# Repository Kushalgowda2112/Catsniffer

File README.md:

# **CatSniffer**

## Overview

CatSniffer 😼 is a multiprotocol, multiband device designed for sniffing, communicating, and attacking IoT (Internet of Things) devices. Shaped as a highly portable USB stick, it integrates powerful chips like **TI CC1352**, **Semtech SX1262**, and either the **RP2040** (for V3 and newer) or **Microchip SAMD21E17** (for V2 and earlier).

This device serves as a comprehensive tool for IoT security researchers, developers, and enthusiasts. CatSniffer is compatible with a wide range of software, including:

- SmartRF Packet Sniffer
- Sniffle
- zigbee2mqtt
- Z-Stack-firmware
- Ubiqua Protocol Analyzer
- Custom applications tailored to your specific needs

---

## Supported Technologies

CatSniffer can operate across multiple protocols:
- **LoRa**
- **Sub-1 GHz**
- **2.4 GHz**

Inspired by the work of Michael Ossmann and tools like the YardStick, GreatFET, HackRF, and Ubertooth, CatSniffer pays homage to the open-source hardware community.

---

## Versions

CatSniffer has evolved through several iterations, each improving on the previous:
- **CatSniffer v1.2**
- **CatSniffer v1.3**
- **CatSniffer v2.0**
- **CatSniffer v2.1**
- **CatSniffer v3.1**

All versions are supported, but newer versions include additional features and enhancements. Firmware for each version is tracked separately within the repository for clarity and ease of access.

---

## Protocols Supported

CatSniffer is compatible with the following protocols:
- **Thread**
- **Zigbee**
- **Bluetooth 5 Low Energy (BLE)**
- **IEEE 802.15.4g**
- **6LoWPAN**
- **LoRa/LoRaWAN**
- **Wi-SUN**
- **Amazon Sidewalk**
- **mioty®**

---

## Features

- **Multiprotocol and Multi-Band:** Operates across LoRa, Sub-1 GHz, and 2.4 GHz frequencies.
- **Auto Programming:** Integrated bootloader from TI CC; no external programmer needed.
- **User-Friendly Design:** Includes LEDs for status, reset buttons, and a general-purpose button.
- **Customizable:** SMA port for antenna selection and support for custom firmware or software development.
- **Cross-Platform Compatibility:** Works with Windows and Linux.

---

## Compatible Software

CatSniffer works with multiple software tools for sniffing and debugging:
- **Smart RF Packet Sniffer 2**
- **Wireshark**
- **Sniffle**
- **zigbee2mqtt**
- **Z-Stack-firmware**
- **pycatsniffer** (Beta)
- **Ubiqua Protocol Analyzer**

---

## Pre-requisites for Building Firmware

- **IDE:** Arduino IDE for RP2040 or SAMD21E17
- **Compiler:** Code Composer Studio (tested with CCS 10.2)
- **SDK:** SimpleLink CC13x2 and CC26x2 SDK
- **Programming Language:** Python 3

---

## License

- **Firmware License:** Released under a **GNU AGPL v3.0** license. See the `LICENSE` file for more information.
- **Hardware License:** Released under a **CERN Open Hardware Licence v1.2**. See the `LICENSE_HARDWARE` file for more details.

---

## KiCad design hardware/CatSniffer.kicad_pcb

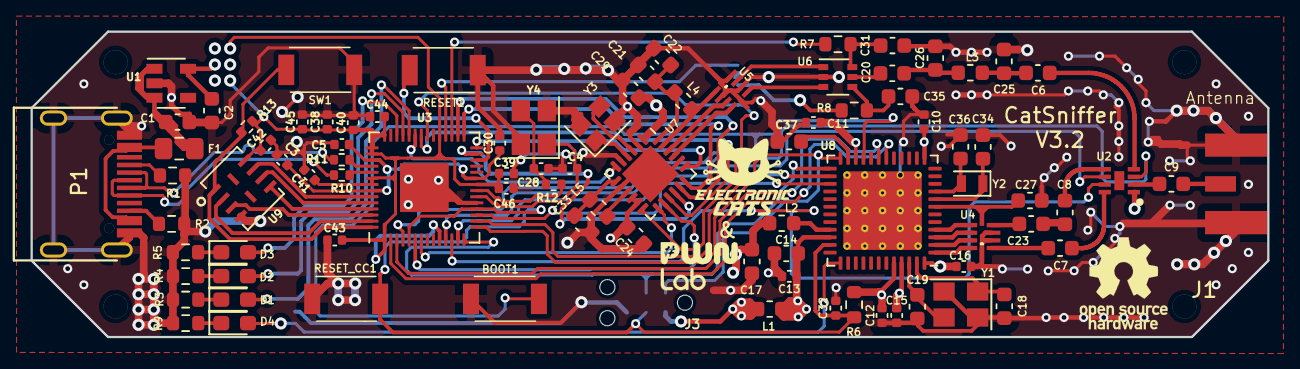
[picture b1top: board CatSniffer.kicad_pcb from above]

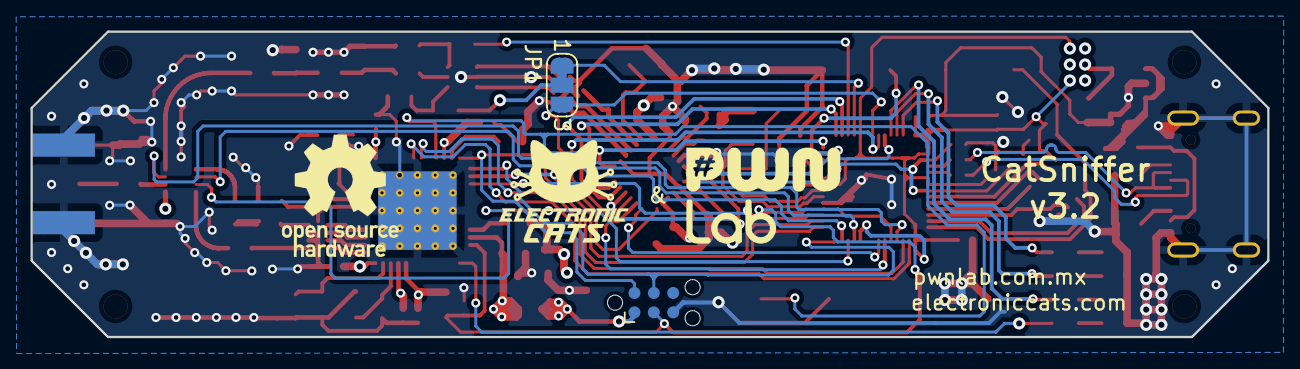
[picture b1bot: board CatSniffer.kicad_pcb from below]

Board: 4 copper layers, 81.0 x 20.0 mm, 90 parts (2 on the bottom side), 88 nets.

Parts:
BOOT1: SW; TS1088R02026
C1, C37: 1uF; C_0603_1608Metric
C2, C21, C24, C29: 0.1uF; C_0603_1608Metric
C3, C38: 1uF; C_0402_1005Metric
C4, C28: 27pF; C_0402_1005Metric
C5, C30, C39, C40, C41, C42, C43, C44, C45, C46: 0.1uF; C_0402_1005Metric
C6, C7, C8, C9, C20, C23, C27: 100pF; C_0603_1608Metric
C10, C11, C12, C13, C15, C16, C32: 100nF; C_0402_1005Metric
C14, C17: 22uF; C_0603_1608Metric
C18, C19: 22pF; C_0603_1608Metric
C22: 47pF; C_0603_1608Metric
C25, C26: 3.3pF; C_0603_1608Metric
C31, C35: 1nF; C_0603_1608Metric
C33: 470nF; C_0603_1608Metric
C34, C36: 10pF; C_0603_1608Metric
D1, D2, D3, D4: LED; LED_0603_1608Metric_Pad1.05x0.95mm_HandSolder
F1: 0.5A; Fuse_0805_2012Metric_Pad1.15x1.40mm_HandSolder
J1: Antenna; SMA_EDGE
J3: Conn_01x06_Female; Tag-Connect_TC2030-IDC-NL_2x03_P1.27mm_Vertical
JP1: Jumper; SolderJumper-3_P1.3mm_Bridged12_RoundedPad1.0x1.5mm_NumberL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
L1: BLM18HE152SN1D; L_0603_1608Metric
L2: 6.8uH; L_0603_1608Metric
L3: 9.1nH; L_0603_1608Metric
L4: 47nH; L_0603_1608Metric
L5: 15uH; L_0603_1608Metric
P1: USB_C_Plug_USB2.0; C393939
R1, R2: 5k1; R_0603_1608Metric
R3, R4, R5, R9: 330; R_0603_1608Metric
R6: 100K; R_0603_1608Metric
R7, R8: 100R; R_0603_1608Metric
R10, R11: 27; R_0402_1005Metric
R12: 1k; R_0402_1005Metric
R13: 10k; R_0402_1005Metric
RESET1: SW; TS1088R02026
RESET_CC1: SW; TS1088R02026
SW1: SW; TS1088R02026
U1: AP2112K-3.3; SOT-23-5
U2: RFSW8006QTR7; SON50P200X200X90-9N
U3: RP2040; QFN-56-1EP_7x7mm_P0.4mm_EP3.2x3.2mm
U4: 0900PC15A0036; 0900FM15D0039E
U5: 0900FM15D0039; 0900FM15D0039E
U6: PE42421; SOT-363_SC-70-6
U7: SX1262IMLTRT; QFN-24-1EP_4x4mm_P0.5mm_EP2.65x2.65mm
U8: CC1352P1F3RGZT; VQFN-48-1EP_7x7mm_P0.5mm_EP5.15x5.15mm_ThermalVias
U9: W25Q16JV; W25Q16JVUUIQ
Y1: 48MHz; Crystal_SMD_3225-4Pin_3.2x2.5mm
Y2: 32.768kHz; Crystal_SMD_2012-2Pin_2.0x1.2mm
Y3: 32Mhz; Crystal_SMD_2520-4Pin_2.5x2.0mm
Y4: 12MHz; Crystal_SMD_3225-4Pin_3.2x2.5mm

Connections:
+1V2: C3.1, C5.1, C30.1, U3.23 (DVDD), U3.45 (VREG_VOUT), U3.50 (DVDD)
+3V3: C2.2, C24.1, C29.1, C38.1, C39.1, C40.1, C41.1, C42.1, C43.1, C44.1, C45.1, C46.1, J3.1, L1.2, R13.1, U1.5 (VOUT), U2.1 (VDD), U3.1 (IOVDD), U3.10 (IOVDD), U3.22 (IOVDD), U3.33 (IOVDD), U3.42 (IOVDD), U3.43 (ADC_AVDD), U3.44 (VREG_IN), U3.48 (USB_VDD), U3.49 (IOVDD), U7.1 (VDD_IN), U7.10 (VBAT), U7.11 (VBAT_IO), U9.8 (VCC)
/2_4_GHZ_RF_N: U4.8 (BP_2_4_GHZ_RF_N), U8.2 (RF_N_2_4GHZ)
/2_4_GHZ_RF_P: U4.9 (BP_2_4_GHZ_RF_P), U8.1 (RF_P_2_4GHZ)
/ANT: C9.2, J1.1 (In)
/ANT_SW: R7.2, U3.31 (GPIO20)
/BOOT: BOOT1.2, U3.4 (GPIO2), U8.21 (DIO_15)
/BUSY: U3.6 (GPIO4), U7.14 (BUSY)
/CIPO: U3.27 (GPIO16), U7.16 (MISO)
/COPI: U3.30 (GPIO19), U7.17 (MOSI)
/CTF1: U2.3 (CRF1), U3.11 (GPIO8)
/CTF2: U2.7 (CRF2), U3.12 (GPIO9)
/CTF3: U2.6 (CRF3), U3.13 (GPIO10)
/D+: P1.A6 (D+), R10.1
/D-: P1.A7 (D-), R11.1
/DCDC_SW: L2.1, U8.33 (DCDC_SW)
/DIO1: U3.7 (GPIO5), U7.13 (DIO1)
/DIO2: JP1.3 (B), U3.35 (GPIO23), U7.12 (DIO2)
/DIO3: U3.37 (GPIO25), U7.6 (DIO3)
/DIO22: JP1.1 (A), U3.32 (GPIO21)
/JTAG/TDI: U3.16 (GPIO13), U8.26 (DIO_16)
/JTAG/TDO: U3.17 (GPIO14), U8.27 (DIO_17)
/LED1: D3.2 (A), U3.40 (GPIO28_ADC2)
/LED2: D2.2 (A), U3.39 (GPIO27_ADC1)
/LED3: D1.2 (A), U3.38 (GPIO26_ADC0)
/LED4: D4.2 (A), U8.37 (DIO_24)
/LORA_O: C6.1, C25.1, L3.1
/NSS: U3.28 (GPIO17), U7.19 (NSS)
/QSPI_SCK: U3.52 (QSPI_SCLK), U9.6 (CLK)
/QSPI_SD0: U3.53 (QSPI_SD0), U9.5 (DI(IO0))
/QSPI_SD1: U3.55 (QSPI_SD1), U9.2 (DO(IO1))
/QSPI_SD2: U3.54 (QSPI_SD2), U9.3 (IO2)
/QSPI_SD3: U3.51 (QSPI_SD3), U9.7 (IO3)
/QSPI_SS: R13.2, SW1.1, U3.56 (QSPI_SS), U9.1 (~CS)
/RESET: RESET1.1, U3.26 (RUN)
/RESET_CC: C32.1, J3.3, R6.1, RESET_CC1.2, U3.5 (GPIO3), U3.18 (GPIO15), U8.35 (~RESET_N)
/RESET_SX: U3.36 (GPIO24), U7.15 (~NRESET)
/RFI_N: U5.3 (RFI_N), U7.22 (RFI_N)
/RFI_P: U5.4 (RFI_P), U7.21 (RFI_P)
/RFO: L4.2, U5.1 (RFO), U7.23 (RFO)
/RXD: U3.3 (GPIO1), U8.19 (DIO_13)
/RX_TX: C27.2, U4.5 (RX_TX), U8.7 (RX_TX)
/SCK: U3.29 (GPIO18), U7.18 (SCK)
/SUB_1_GHZ_RF_N: U4.6 (BP_SUB1-_GHZ_RF_N), U8.4 (RF_N_SUB_1GHZ)
/SUB_1_GHZ_RF_P: U4.7 (BP_SUB1-_GHZ_RF_P), U8.3 (RF_P_SUB_1GHZ)
/SW_RFI: U5.6 (SW_RFI), U6.3 (RF2)
/SW_RFO: U5.8 (SW_RFO), U6.1 (RF1)
/TXD: U3.2 (GPIO0), U8.18 (DIO_12)
/UBP_2_4_GHZ: C7.1, U4.1 (UBP_2_4_GHZ)
/UBP_SUB-1_GHZ: C8.1, C23.1
/VDDR: C15.1, C16.1, C17.1, L2.2, U8.45 (VDDR), U8.48 (VDDR_RF)
/VDDS: C10.1, C11.1, C12.1, C13.1, C14.1, L1.1, R6.2, U8.13 (VDDS2), U8.22 (VDDS3), U8.34 (VDDS_DCDC), U8.44 (VDDS)
/X48M_N: C19.1, U8.46 (X48M_N), Y1.3
/X48M_P: C18.1, U8.47 (X48M_P), Y1.1
/XTA: U7.3 (XTA), Y3.3
/XTB: U7.4 (XTB), Y3.1
/cJTAG_TCK: J3.4, U3.14 (GPIO11), U8.25 (JTAG_TCKC)
/cJTAG_TMSC: J3.2, U3.15 (GPIO12), U8.24 (JTAG_TMSC)
GND: BOOT1.1, C1.1, C2.1, C3.2, C4.2, C5.2, C10.2, C11.2, C12.2, C13.2, C14.2, C15.2, C16.2, C17.2, C18.2, C19.2, C21.2, C22.2, C24.2, C25.2, C26.2, C27.1, C28.2, C29.2, C30.2, C31.2, C32.2, C33.2, C34.2, C35.2, C36.2, C37.2, C38.2, C39.2, C40.2, C41.2, C42.2, C43.2, C44.2, C45.2, C46.2, J1.2 (Ext), J3.5, P1.A1 (GND), P1.S1 (SHIELD), R1.1, R2.1, R3.1, R4.1, R5.1, R9.1, RESET1.2, RESET_CC1.1, SW1.2, U1.2 (GND), U3.19 (TESTEN), U3.57 (GND), U4.2 (GND), U4.3 (GND), U4.10 (GND), U5.2 (GND), U5.5 (GND), U5.7 (GND), U5.9 (GND), U5.10 (GND), U6.2 (GND), U7.2 (GND), U7.5 (GND), U7.8 (GND), U7.20 (GND), U8.49 (EGP), U9.4 (GND), Y1.2, Y1.4, Y3.2, Y3.4, Y4.2, Y4.4
unnamed: C20.2, C26.1, L3.2
unnamed: C28.1, R12.1, Y4.3
unnamed: D1.1 (K), R3.2
unnamed: D2.1 (K), R4.2
unnamed: D3.1 (K), R5.2
unnamed: D4.1 (K), R9.2
unnamed: F1.1, P1.A4 (VBUS)
unnamed: JP1.2 (C), R8.2
unnamed: P1.A5 (CC), R1.2
unnamed: P1.B5 (VCONN), R2.2
unnamed: C9.1, U2.2 (ANT)
unnamed: C6.2, U2.4 (RF1)
unnamed: C7.2, U2.8 (RF2)
unnamed: C8.2, U2.5 (RF3)
unnamed: R11.2, U3.46 (USB_DM)
unnamed: R10.2, U3.47 (USB_DP)
unnamed: C4.1, U3.20 (XIN), Y4.1
unnamed: R12.2, U3.21 (XOUT)
unnamed: C23.2, U4.4 (UBP_SUB-1_GHZ)
unnamed: C20.1, U6.5 (RFC)
unnamed: C31.1, R7.1, U6.6 (V1)
unnamed: C35.1, R8.1, U6.4 (V2)
unnamed: L5.1, U7.9 (DCC_SW)
unnamed: C33.1, L5.2, U7.7 (VREG)
unnamed: C21.1, C22.1, L4.1, U7.24 (VR_PA)
unnamed: C37.1, U8.23 (DCOUPL)
unnamed: C34.1, U8.8 (X32K_Q1), Y2.1
unnamed: C36.1, U8.9 (X32K_Q2), Y2.2
VCC: C1.2, F1.2, U1.1 (VIN), U1.3 (EN)

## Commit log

2024-12-28 files uploaded
